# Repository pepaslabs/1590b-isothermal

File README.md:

# 1590b-isothermal

A "daughter board" which attaches to the bottom of a Hammond 1590B and regulates its temperature at 25C.

- [schematic](kicad/releases/v1/isothermal.pdf)
- [gerber files](kicad/releases/v1)
- [OSHPark link](https://oshpark.com/shared_projects/qRlewBCr)

The resistor values were chosen to map a 20C to 30C window onto (roughly) 0V to 3.3V.

See also [this link](https://github.com/cellularmitosis/logs/tree/master/20180126-25c-chamber-tuning) for PID tuning and measurements of a similar design (based on MCP9701 rather than thermistors).

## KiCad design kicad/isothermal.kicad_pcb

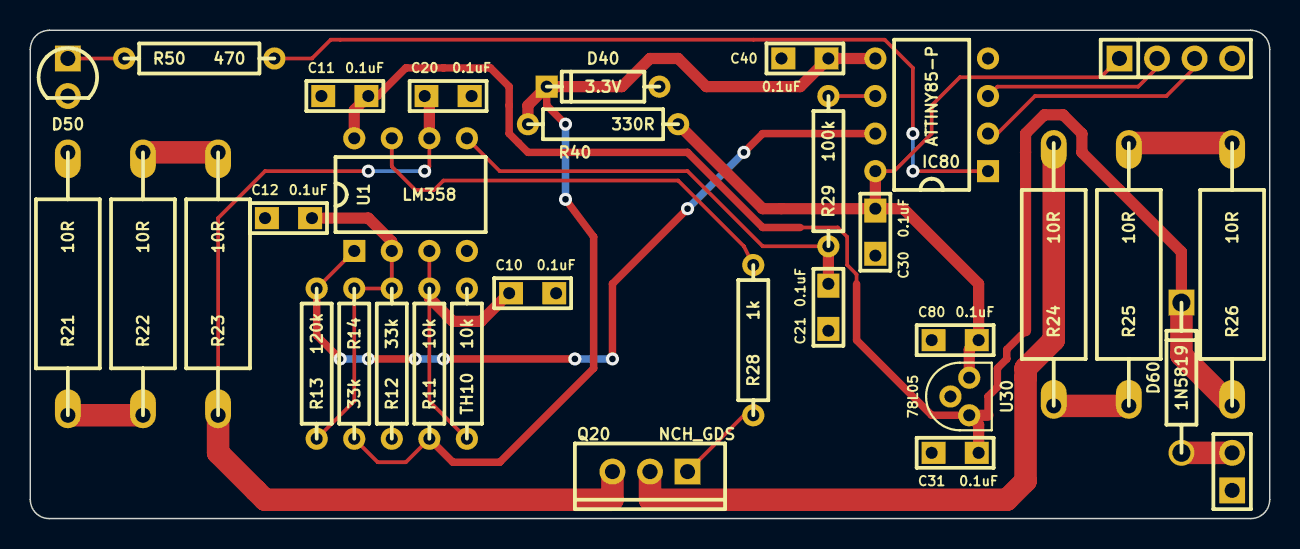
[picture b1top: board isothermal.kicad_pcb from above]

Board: 2 copper layers, 83.8 x 33.0 mm, 33 parts (0 on the bottom side), 22 nets.

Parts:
C10, C11, C12, C20, C21, C30, C31, C40, C80: 0.1uF; CERCAP_15_059B_0805
D40: 3.3V; DIODE_SS_059A_03_PL
D50: LED; LED_3MM_069A
D60: 1N5819; DIODE_1A_069A_04_PL
IC80: ATTINY85-P; DIP8_059A_PL
P60: CONN_2X1; SIL-2
P70: CONN_4X1; SIL-4
Q20: NCH_GDS; TO-220_V_069A
R11: 10k; R_AXIAL_0W25_059A_PL
R12, R14: 33k; R_AXIAL_0W25_059A_PL
R13: 120k; R_AXIAL_0W25_059A_PL
R21, R22, R23, R24, R25, R26: 10R; R_AXIAL_1W_PL
R28: 1k; R_AXIAL_0W25_059A_PL
R29: 100k; R_AXIAL_0W25_059A_PL
R40: 330R; R_AXIAL_0W25_059A_PL
R50: 470; R_AXIAL_0W25_059A_PL
TH10: 10k; R_AXIAL_0W25_059A_PL
U1: LM358; DIP8_059A_PL
U30: 78L05; TO-92_U_059A_PL

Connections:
3V3: C40.1, D40.2, IC80.5, R11.1, R14.2, R40.1
5V: C30.1, C80.1, IC80.8, P70.1, R40.2, U30.3
12V: C11.1, C31.1, D60.2, R26.2, U1.8, U30.1
ADC: IC80.7, R13.2, U1.1
GND: C10.2, C11.2, C12.2, C20.2, C21.2, C30.2, C31.2, C40.2, C80.2, D40.1, D50.2, IC80.4, P60.1, P70.4, R12.1, R21.1, TH10.2, U1.4, U30.2
LED: IC80.1, R50.2
unnamed: D60.1, P60.2
unnamed: D50.1, R50.1
unnamed: R22.2, R23.1
unnamed: R21.2, R22.1
unnamed: R25.2, R26.1
unnamed: R24.2, R25.1
unnamed: Q20.2, R24.1
unnamed: C21.1, R29.1, U1.5
unnamed: R28.2, U1.7
unnamed: Q20.1, R28.1
unnamed: C20.1, Q20.3, R23.2, U1.6
unnamed: C10.1, R11.2, TH10.1, U1.3
unnamed: C12.1, R12.2, R13.1, R14.1, U1.2
PWM: IC80.6, R29.2
RX: IC80.2, P70.3
TX: IC80.3, P70.2

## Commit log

2018-02-11 board shots
2018-02-11 README
2018-02-11 used wider holes for the input protection diode.
2018-03-04 adding bootloader
2018-03-04 attiny sketch
